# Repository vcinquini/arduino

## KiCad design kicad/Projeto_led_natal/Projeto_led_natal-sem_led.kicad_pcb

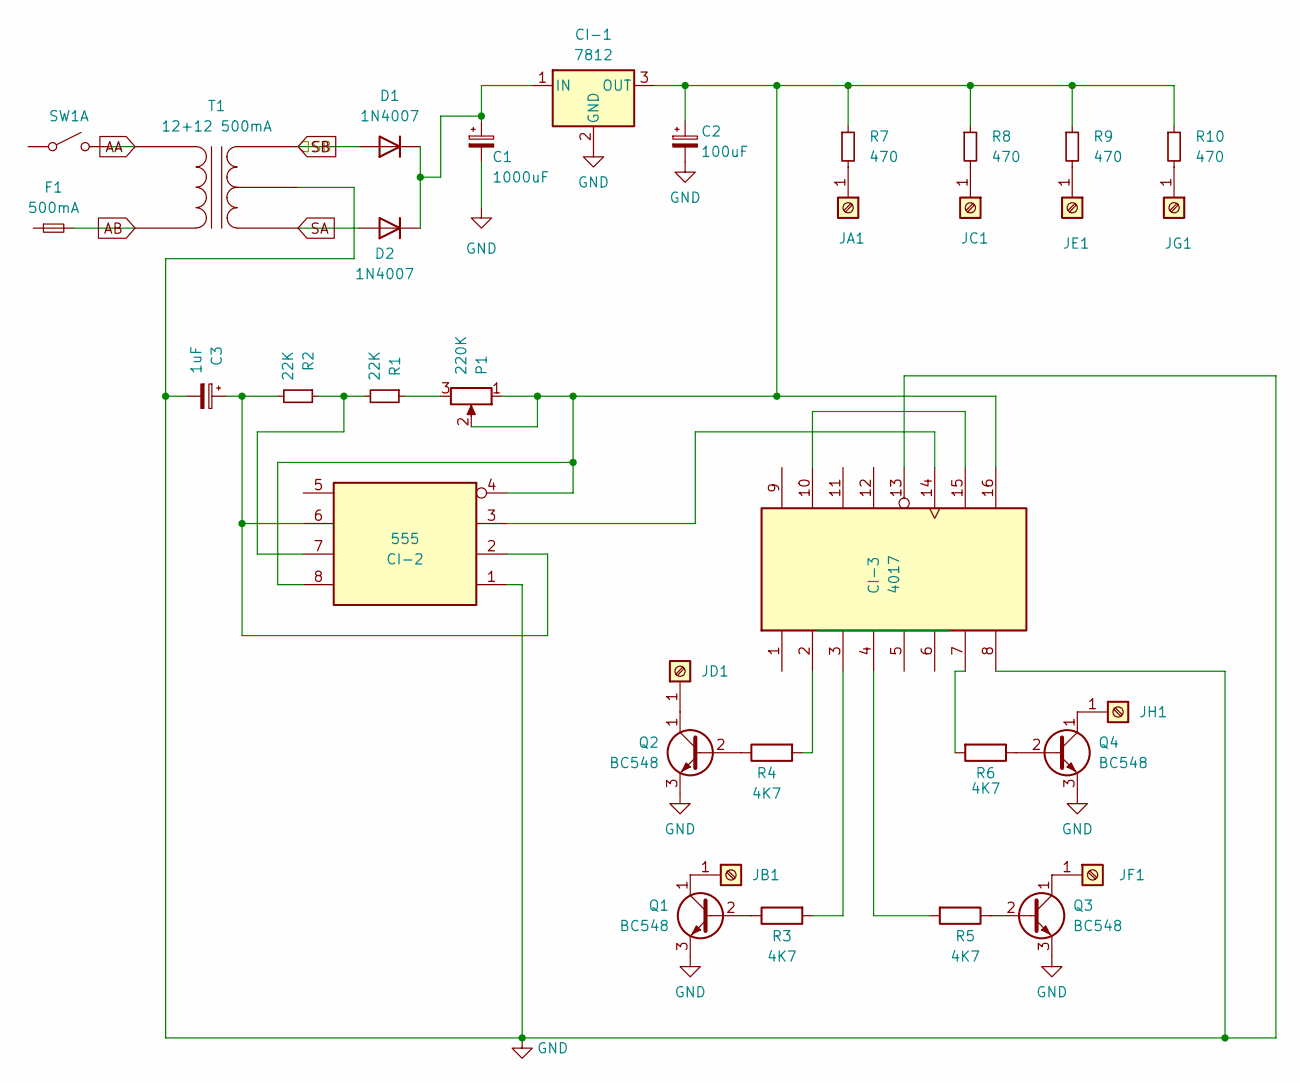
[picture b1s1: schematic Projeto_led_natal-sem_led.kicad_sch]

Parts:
C1: 1000uF; CP_Elec_8x5.4
C2: 100uF; CP_Elec_8x6.2
C3: 1uF; CP_Radial_D10.0mm_P2.50mm
CI-1: 7812; TO-3P-3_Vertical
CI-2: 555; CERDIP-8_W7.62mm_SideBrazed
CI-3: 4017; DIP-16_W10.16mm
D1, D2: 1N4007; D_T-1_P10.16mm_Horizontal
F1: 500mA; Fuse_1812_4532Metric
JA1: Screw_Terminal_01x01
JB1: Screw_Terminal_01x01; SolderWire-0.5sqmm_1x01_D0.9mm_OD2.1mm
JC1: Screw_Terminal_01x01
JD1: Screw_Terminal_01x01; SolderWire-0.5sqmm_1x01_D0.9mm_OD2.1mm
JE1: Screw_Terminal_01x01; SolderWire-0.5sqmm_1x01_D0.9mm_OD2.1mm
JF1: Screw_Terminal_01x01; SolderWire-0.5sqmm_1x01_D0.9mm_OD2.1mm
JG1: Screw_Terminal_01x01; SolderWire-0.5sqmm_1x01_D0.9mm_OD2.1mm
JH1: Screw_Terminal_01x01; SolderWire-0.5sqmm_1x01_D0.9mm_OD2.1mm
P1: 220K; Potentiometer_Vishay_T93YA_Vertical
Q1, Q2, Q3, Q4: BC548; TO-92L_Inline
R1, R2: 22K; R_Axial_DIN0204_L3.6mm_D1.6mm_P5.08mm_Vertical
R3, R4, R5, R6: 4K7; R_Axial_DIN0204_L3.6mm_D1.6mm_P1.90mm_Vertical
R7, R8, R9, R10: 470; R_Axial_DIN0204_L3.6mm_D1.6mm_P1.90mm_Vertical
SW1: SW_DIP_SPSTx01_Slide_6.7x4.1mm_W6.73mm_P2.54mm_LowProfile_J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
T1: 12+12 500mA; Transformer_MACOM_SM-22

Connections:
AA: SW1.2 (B), T1.1 (AA)
AB: F1.2, T1.2 (AB)
GND: C1.2, C2.2, C3.2, CI-1.2 (GND), CI-2.1 (GND), CI-3.8 (VSS), CI-3.13 (CKEN), Q1.3 (E), Q2.3 (E), Q3.3 (E), Q4.3 (E), T1.4 (SC)
unnamed: C1.1, CI-1.1 (IN), D1.1 (K), D2.1 (K)
unnamed: C2.1, CI-1.3 (OUT), CI-2.4 (R), CI-2.8 (VCC), CI-3.16 (VDD), P1.1, P1.2, R7.1, R8.1, R9.1, R10.1
unnamed: CI-2.7 (DIS), R1.2, R2.1
unnamed: CI-2.3 (Q), CI-3.14 (CLK)
unnamed: C3.1, CI-2.2 (TR), CI-2.6 (THR), R2.2
unnamed: CI-3.3 (Q0), R3.2
unnamed: CI-3.2 (Q1), R4.2
unnamed: CI-3.4 (Q2), R5.2
unnamed: CI-3.7 (Q3), R6.2
unnamed: CI-3.10 (Q4), CI-3.15 (Reset)
unnamed: JA1.1, R7.2
unnamed: JB1.1, Q1.1 (C)
unnamed: JC1.1, R8.2
unnamed: JD1.1, Q2.1 (C)
unnamed: JE1.1, R9.2
unnamed: JF1.1, Q3.1 (C)
unnamed: JG1.1, R10.2
unnamed: JH1.1, Q4.1 (C)
unnamed: P1.3, R1.1
unnamed: Q1.2 (B), R3.1
unnamed: Q2.2 (B), R4.1
unnamed: Q3.2 (B), R5.1
unnamed: Q4.2 (B), R6.1
SA: D2.2 (A), T1.3 (SA)
SB: D1.2 (A), T1.5 (SB)

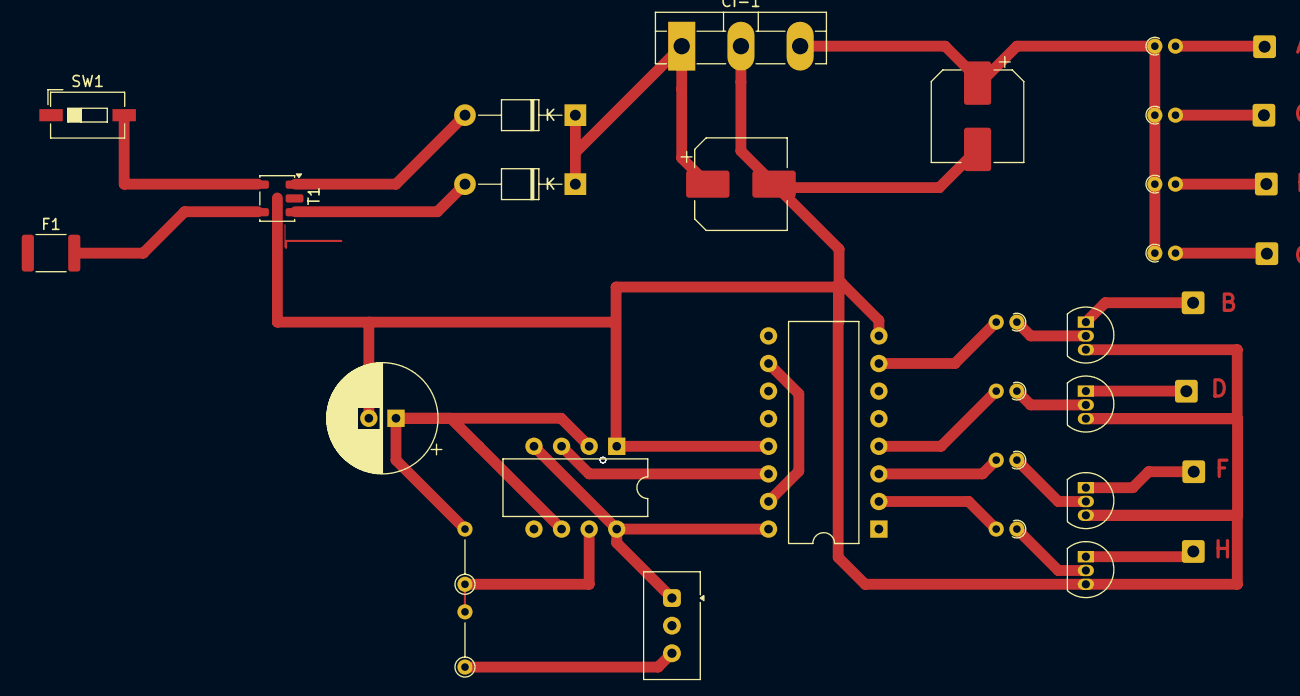
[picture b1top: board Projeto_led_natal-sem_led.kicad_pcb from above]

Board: 2 copper layers, 34 parts (0 on the bottom side), 27 nets.

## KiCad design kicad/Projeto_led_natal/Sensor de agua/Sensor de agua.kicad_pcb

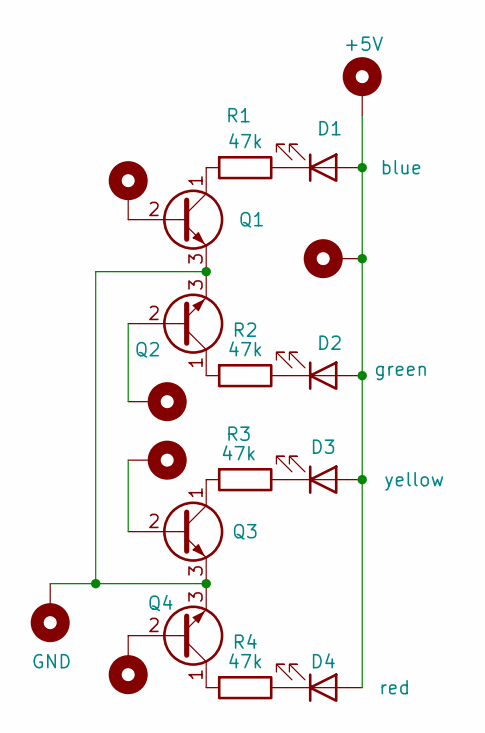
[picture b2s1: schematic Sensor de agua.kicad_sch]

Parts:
D1: blue; LED_D5.0mm
D2: green; LED_D5.0mm
D3: yellow; LED_D5.0mm
D4: red; LED_D5.0mm
H1, H2, H3, H4, H6: MountingHole_Pad; SolderWire-0.5sqmm_1x01_D0.9mm_OD2.1mm
H5: GND; SolderWire-0.5sqmm_1x01_D0.9mm_OD2.1mm
H7: +5V; SolderWire-0.5sqmm_1x01_D0.9mm_OD2.1mm
Q1, Q2, Q3, Q4: TO-92_Inline
R1, R2, R3, R4: 47k; R_Axial_DIN0204_L3.6mm_D1.6mm_P5.08mm_Horizontal

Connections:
unnamed: D1.2 (A), D2.2 (A), D3.2 (A), D4.2 (A), H6.1, H7.1
unnamed: D1.1 (K), R1.1
unnamed: D2.1 (K), R2.1
unnamed: D3.1 (K), R3.1
unnamed: D4.1 (K), R4.1
unnamed: H1.1, Q1.2 (B)
unnamed: Q1.1 (C), R1.2
unnamed: H5.1, Q1.3 (E), Q2.3 (E), Q3.3 (E), Q4.3 (E)
unnamed: H2.1, Q2.2 (B)
unnamed: Q2.1 (C), R2.2
unnamed: H3.1, Q3.2 (B)
unnamed: Q3.1 (C), R3.2
unnamed: H4.1, Q4.2 (B)
unnamed: Q4.1 (C), R4.2

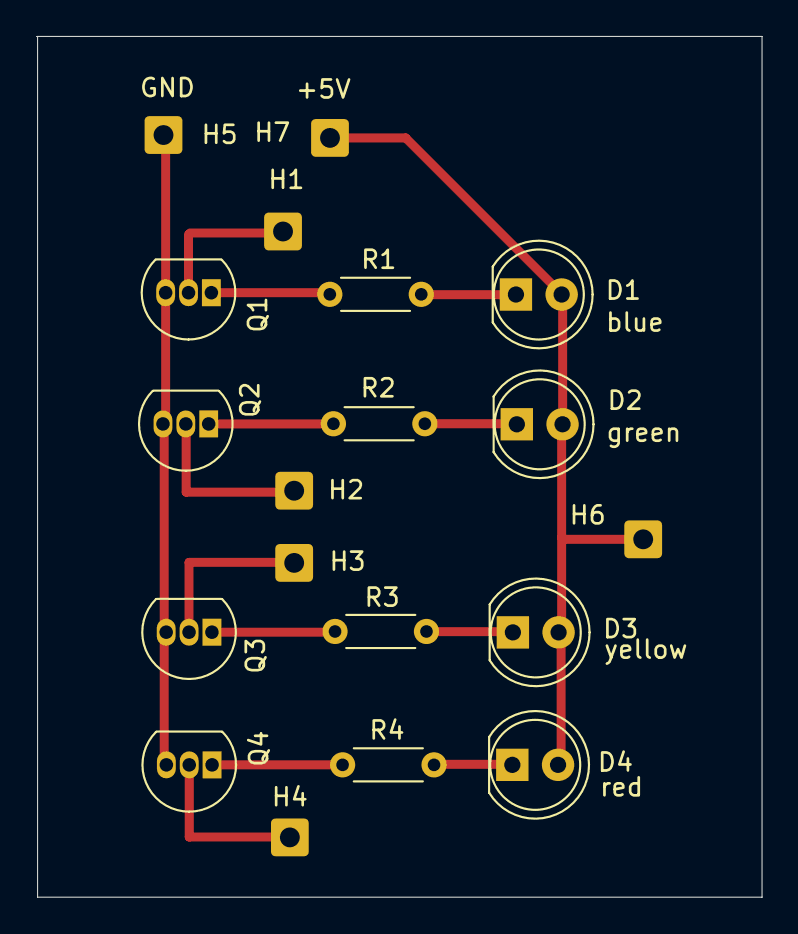
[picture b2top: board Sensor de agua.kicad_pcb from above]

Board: 2 copper layers, 40.3 x 47.8 mm, 19 parts (0 on the bottom side), 14 nets.

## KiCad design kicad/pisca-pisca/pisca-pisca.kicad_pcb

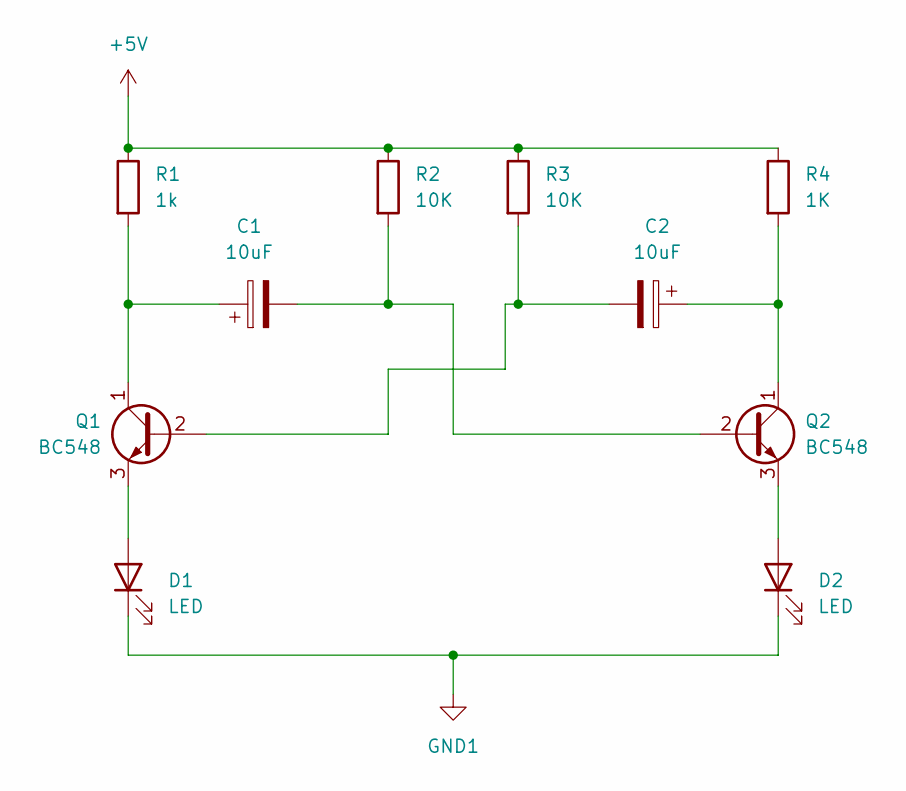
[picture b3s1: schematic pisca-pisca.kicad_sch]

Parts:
C1, C2: 10uF; C_Elec_4x5.4
D1, D2: LED; LED_D1.8mm_W1.8mm_H2.4mm_Horizontal_O1.27mm_Z1.6mm
Q1, Q2: BC548; TO-92_Inline
R1: 1k; R_Axial_DIN0204_L3.6mm_D1.6mm_P1.90mm_Vertical
R2, R3: 10K; R_Axial_DIN0204_L3.6mm_D1.6mm_P1.90mm_Vertical
R4: 1K; R_Axial_DIN0204_L3.6mm_D1.6mm_P1.90mm_Vertical

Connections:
+5V: R1.1, R2.1, R3.1, R4.1
GND1: D1.1 (K), D2.1 (K)
unnamed: D1.2 (A), Q1.3 (E)
unnamed: D2.2 (A), Q2.3 (E)
unnamed: C2.2, Q1.2 (B), R3.2
unnamed: C1.1, Q1.1 (C), R1.2
unnamed: C1.2, Q2.2 (B), R2.2
unnamed: C2.1, Q2.1 (C), R4.2

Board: 2 copper layers, 10 parts (0 on the bottom side), 8 nets, no tracks yet.

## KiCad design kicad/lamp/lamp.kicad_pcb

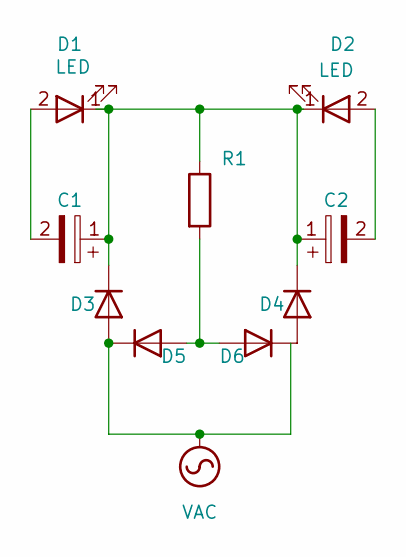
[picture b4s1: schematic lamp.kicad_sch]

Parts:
C1, C2: 100uF; CP_Radial_D6.3mm_P2.50mm
D1, D2: LED; LED_D3.0mm
D3, D4, D5, D6: 1N4007; D_DO-41_SOD81_P10.16mm_Horizontal
R1: 560; R_Axial_Shunt_L22.2mm_W8.0mm_PS14.30mm_P25.40mm

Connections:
unnamed: C1.2, D1.2 (A)
unnamed: C1.1, C2.1, D1.1 (K), D2.1 (K), D3.1 (K), D4.1 (K), R1.1
unnamed: C2.2, D2.2 (A)
unnamed: D4.2 (A), D6.1 (K)
unnamed: D5.2 (A), D6.2 (A), R1.2
VAC: D3.2 (A), D5.1 (K)

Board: 2 copper layers, 9 parts (0 on the bottom side), 6 nets, no tracks yet.

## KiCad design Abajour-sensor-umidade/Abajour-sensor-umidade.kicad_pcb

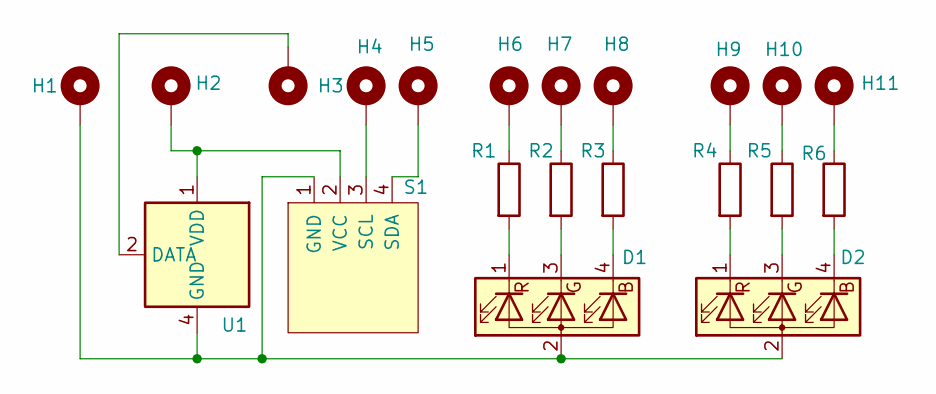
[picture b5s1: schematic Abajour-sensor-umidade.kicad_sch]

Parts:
D1, D2: LED_RAGB; LED_D5.0mm-4_RGB
H1, H2, H3, H4, H5, H6, H7, H8, H9, H10, H11: MountingHole_Pad; MountingHole_3.5mm_Pad
R1, R2, R3, R4, R5, R6: 220; R_Axial_DIN0204_L3.6mm_D1.6mm_P5.08mm_Horizontal
S1: SSD1306; Adafruit_SSD1306 0.96 12c
U1: DHT11; Aosong_DHT11_5.5x12.0_P2.54mm

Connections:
unnamed: D1.2 (A), D2.2 (A), H1.1, S1.1 (GND), U1.4 (GND)
unnamed: D1.4 (BK), R3.2
unnamed: D1.3 (GK), R2.2
unnamed: D1.1 (RK), R1.2
unnamed: D2.4 (BK), R6.2
unnamed: D2.3 (GK), R5.2
unnamed: D2.1 (RK), R4.2
unnamed: H6.1, R1.1
unnamed: H7.1, R2.1
unnamed: H8.1, R3.1
unnamed: H9.1, R4.1
unnamed: H10.1, R5.1
unnamed: H11.1, R6.1
unnamed: H4.1, S1.3 (SCL)
unnamed: H5.1, S1.4 (SDA)
unnamed: H2.1, S1.2 (VCC), U1.1 (VDD)
unnamed: H3.1, U1.2 (DATA)

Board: 2 copper layers, 21 parts (0 on the bottom side), 17 nets, no tracks yet.

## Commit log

2025-10-30 from gft
2025-10-30 from note-valmir
2025-10-30 from note-valmir 2
